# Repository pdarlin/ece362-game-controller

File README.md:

# ECE 362 Handheld Game Console

## Project Description

An RP2350-based handheld gaming console developed for Purdue University's ECE 362 Microprocessor Systems and Interfacing course.

The console features a 2.8-inch SPI TFT LCD, microSD card storage, motion controls, dual analog joysticks, a D-pad, action buttons, PWM haptic feedback, and audio output through a passive buzzer.

## Project Objectives

### 1. Game Display (SPI)
- Interface with a 2.8-inch ILI9341 TFT LCD (240 × 320).
- Display game graphics, menus, and user interfaces.
- Implement SPI communication for screen updates.

### 2. Game Storage (SPI)
- Interface with a microSD card for external storage.
- Implement file reading for game assets and data.

### 3. Motion Control (I2C)
- Interface with the MPU motion sensor using I2C.
- Read accelerometer and gyroscope data.
- Implement motion-based game controls.

### 4. Audio and Haptic Feedback (PWM)
- Generate sound effects using a passive buzzer.
- Control vibration motors using PWM.
- Implement adjustable vibration intensity for game events.

## Additional Features

- Dual analog joysticks
- D-pad and tactile action buttons
- Custom PCB designed using KiCad
- Modular firmware using the Raspberry Pi Pico SDK

## Firmware Structure

```text
firmware/
├── include/
│   ├── audio.h
│   ├── buttons.h
│   ├── display.h
│   ├── game.h
│   ├── gyro.h
│   ├── haptic.h
│   ├── joystick.h
│   └── sdcard.h
├── src/
│   ├── audio.c
│   ├── buttons.c
│   ├── display.c
│   ├── game.c
│   ├── gyro.c
│   ├── haptic.c
│   ├── joystick.c
│   ├── main.c
│   └── sdcard.c
└── platformio.ini
```

*Some firmware modules are still under development.*

## Development Tools

- **Microcontroller:** Raspberry Pi RP2350
- **Programming Language:** C
- **Framework:** Raspberry Pi Pico SDK
- **Build System:** PlatformIO
- **PCB Design:** KiCad

## Team Members

- Pierson Darling
- Tejas Menmow
- Tristan Paul
- Alex Chen

## Project Status

In development — Fall 2026.

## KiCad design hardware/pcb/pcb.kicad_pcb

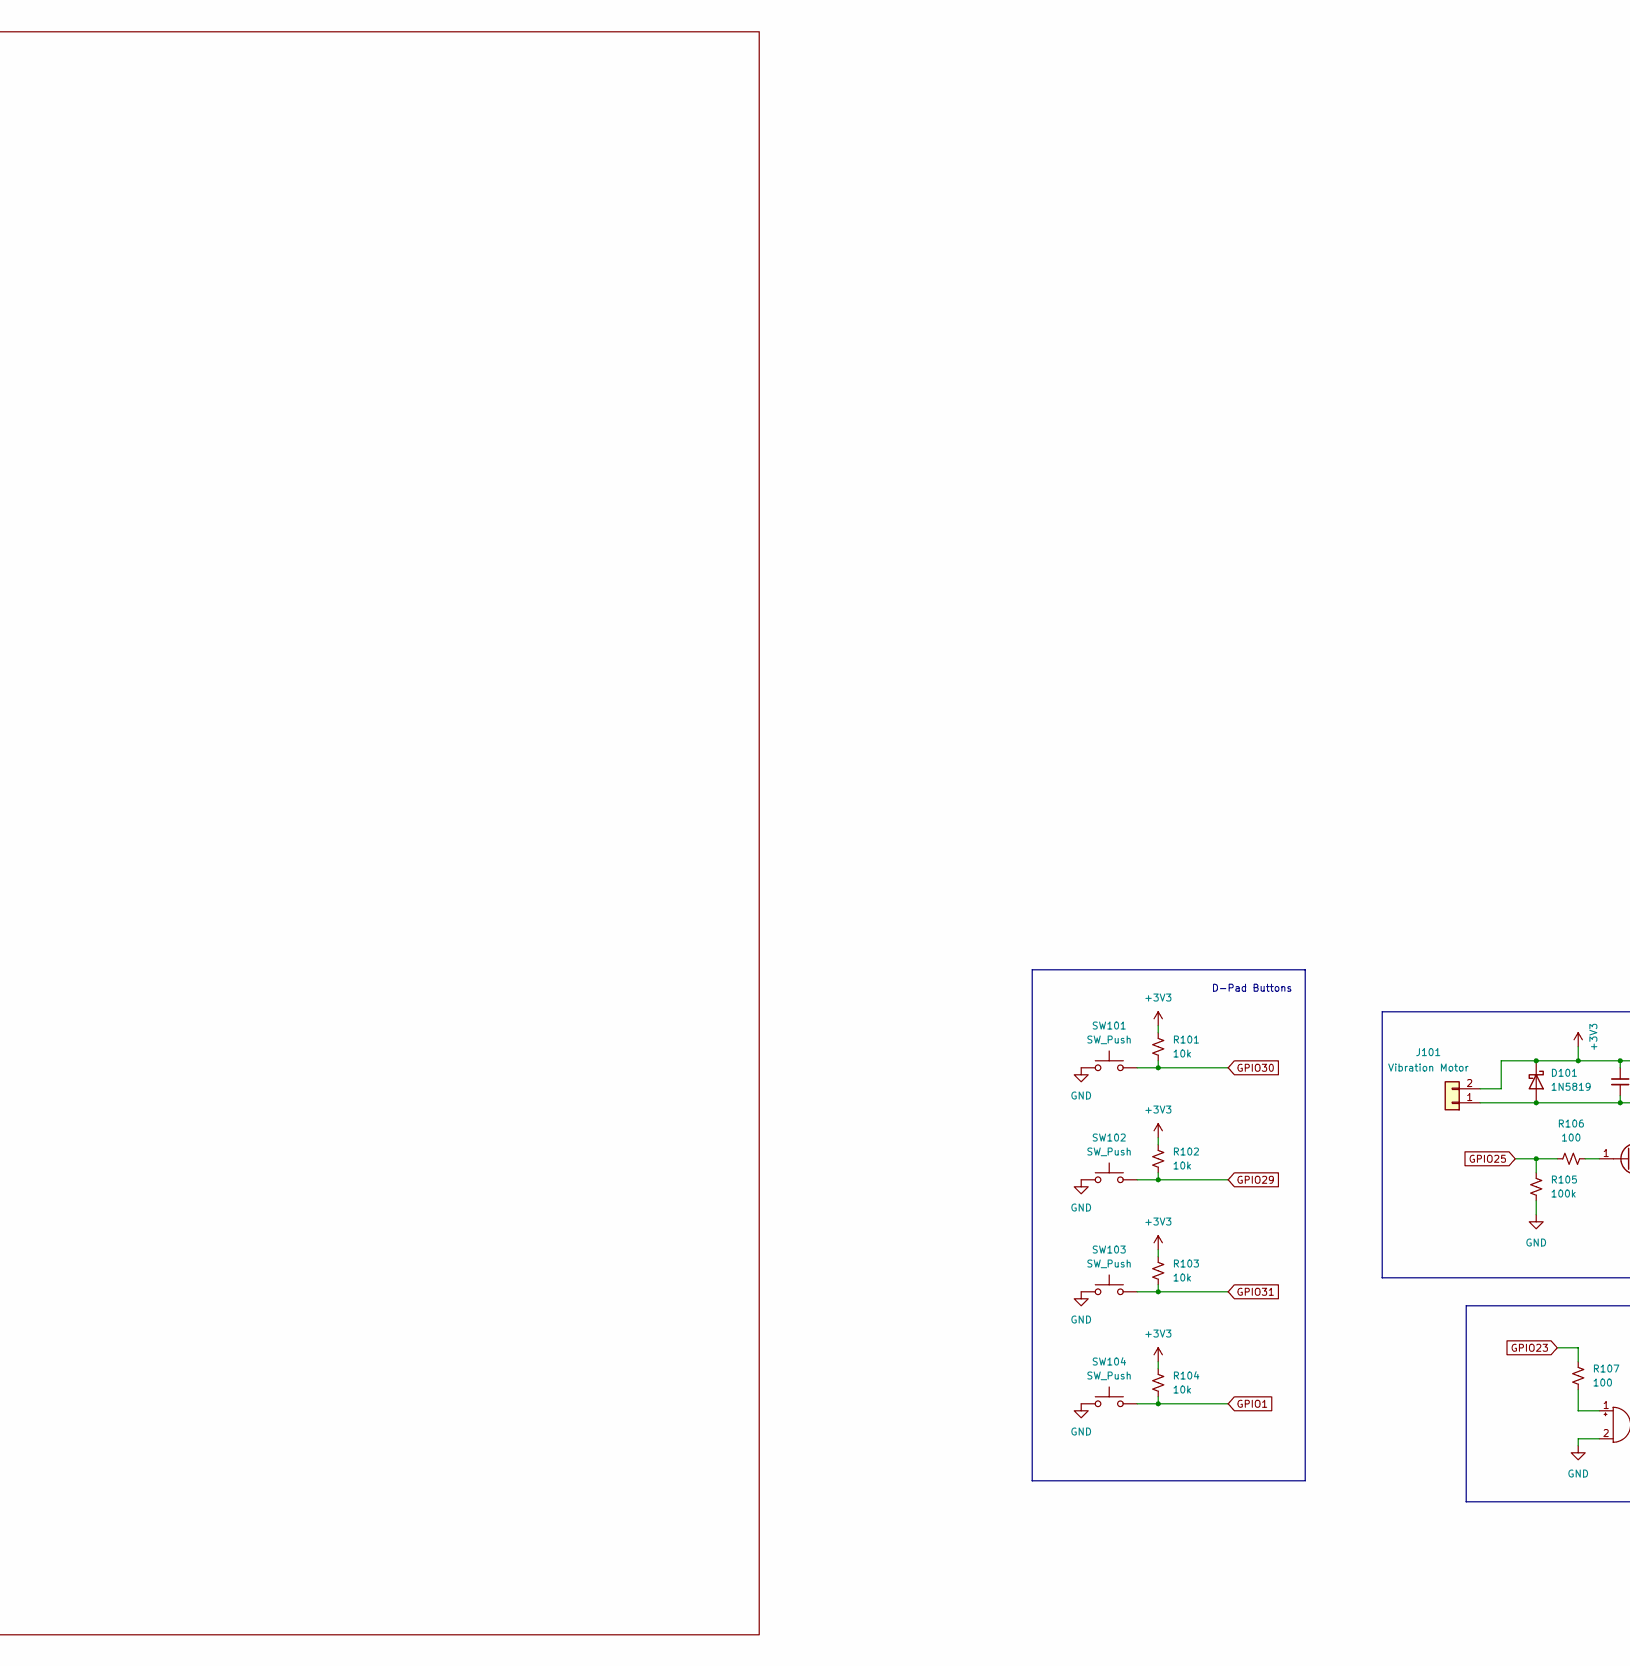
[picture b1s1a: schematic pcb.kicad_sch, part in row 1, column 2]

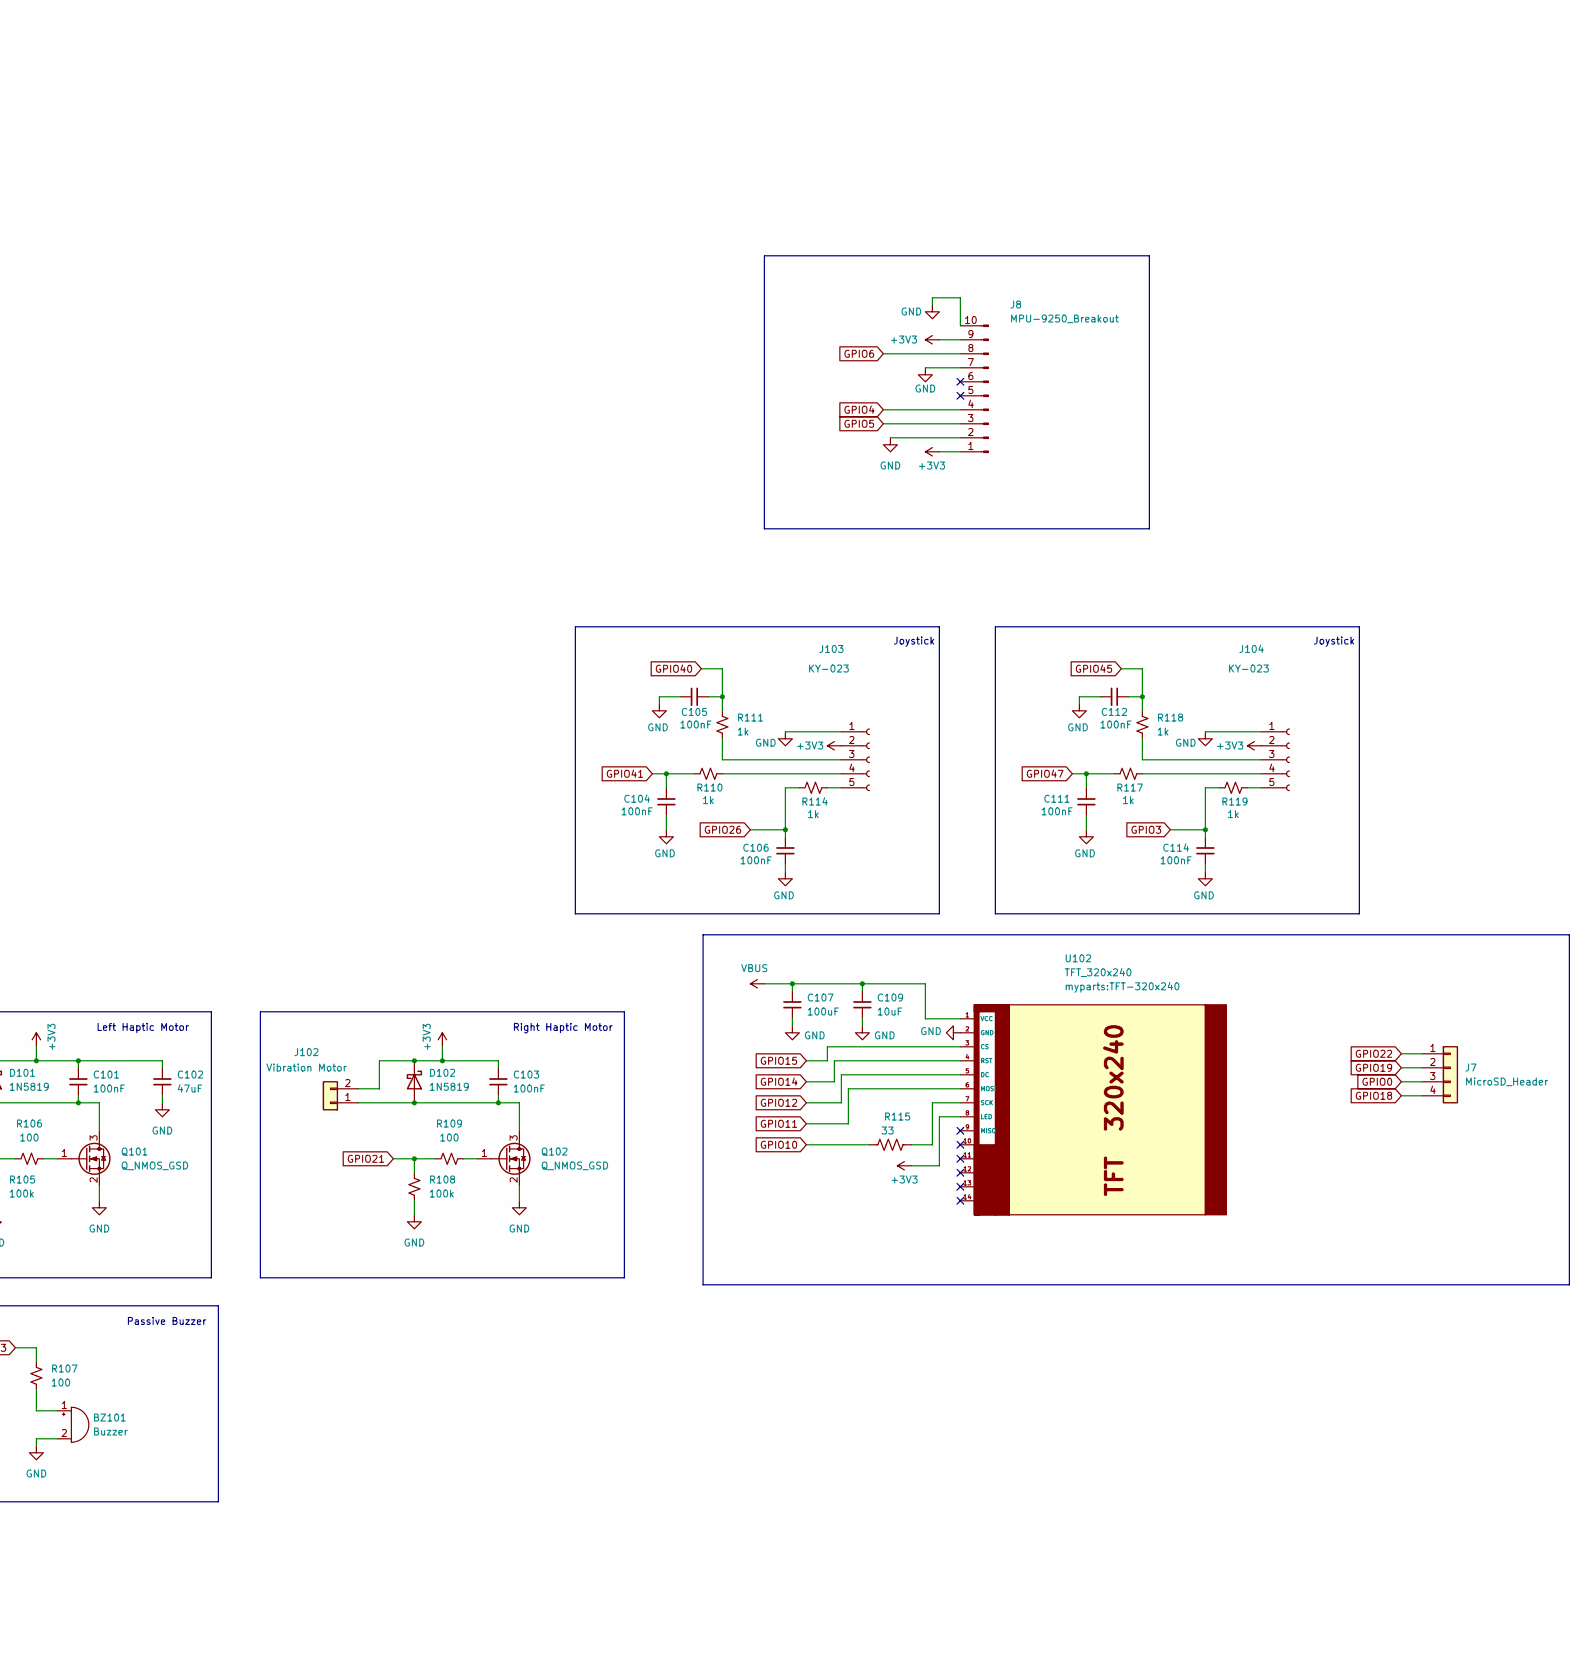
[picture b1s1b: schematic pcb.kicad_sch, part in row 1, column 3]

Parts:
BZ101: Buzzer; Buzzer_12x9.5RM7.6
C101, C103, C104, C105, C106, C111, C112, C114: 100nF; C_Disc_D5.0mm_W2.5mm_P5.00mm
C102: 47uF; CP_Radial_D6.3mm_P2.50mm
C107: 100uF; CP_Radial_D6.3mm_P2.50mm
C109: 10uF; C_Disc_D5.0mm_W2.5mm_P5.00mm
D101, D102: 1N5819; D_DO-41_SOD81_P10.16mm_Horizontal
J7: MicroSD_Header
J8: MPU-9250_Breakout
J101, J102: Vibration Motor; PinHeader_1x02_P2.54mm_Vertical
J103, J104: KY-023; PinSocket_1x05_P2.54mm_Vertical
Q101, Q102: Q_NMOS_GSD; SOT-23
R101, R102, R103, R104: 10k; R_0805_2012Metric
R105, R108: 100k; R_0805_2012Metric
R106, R107, R109: 100; R_0805_2012Metric
R110, R111, R114, R117, R118, R119: 1k; R_0805_2012Metric
R115: 33; R_0805_2012Metric
SW101, SW102, SW103, SW104: SW_Push; SW_PUSH_6mm
U102: TFT_320x240; TFT-320x240

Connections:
GND: BZ101.2 (-), C102.2, C104.1, C105.2, C106.1, C107.2, C109.2, C111.1, C112.2, C114.1, J8.2, J8.7, J8.10, J103.1, J104.1, Q101.2 (S), Q102.2 (S), R105.2, R108.2, SW101.1, SW102.1, SW103.1, SW104.1, U102.2 (GND); also elsewhere on the board
GPIO1: R104.2, SW104.2; also elsewhere on the board
GPIO3: C114.2, R119.1; also elsewhere on the board
GPIO10: R115.2; also elsewhere on the board
GPIO11: U102.6 (MOSI); also elsewhere on the board
GPIO12: U102.5 (DC); also elsewhere on the board
GPIO14: U102.4 (RST); also elsewhere on the board
GPIO15: U102.3 (CS); also elsewhere on the board
GPIO21: R108.1, R109.2; also elsewhere on the board
GPIO23: R107.2; also elsewhere on the board
GPIO25: R105.1, R106.2; also elsewhere on the board
GPIO26: C106.2, R114.1; also elsewhere on the board
GPIO29: R102.2, SW102.2; also elsewhere on the board
GPIO30: R101.2, SW101.2; also elsewhere on the board
GPIO40: C105.1, R111.2; also elsewhere on the board
GPIO41: C104.2, R110.1; also elsewhere on the board
GPIO45: C112.1, R118.2; also elsewhere on the board
GPIO47: C111.2, R117.1; also elsewhere on the board
unnamed: BZ101.1 (+), R107.1
unnamed: C101.2, D101.2 (A), J101.1, Q101.3 (D)
unnamed: C103.2, D102.2 (A), J102.1, Q102.3 (D)
unnamed: J103.3, R111.1
unnamed: J103.4, R110.2
unnamed: J103.5, R114.2
unnamed: J104.3, R118.1
unnamed: J104.4, R117.2
unnamed: J104.5, R119.2
unnamed: Q101.1 (G), R106.1
unnamed: Q102.1 (G), R109.1
unnamed: R115.1, U102.7 (SCK)

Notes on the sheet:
Joystick
Right Haptic Motor
Left Haptic Motor
D-Pad Buttons
Passive Buzzer

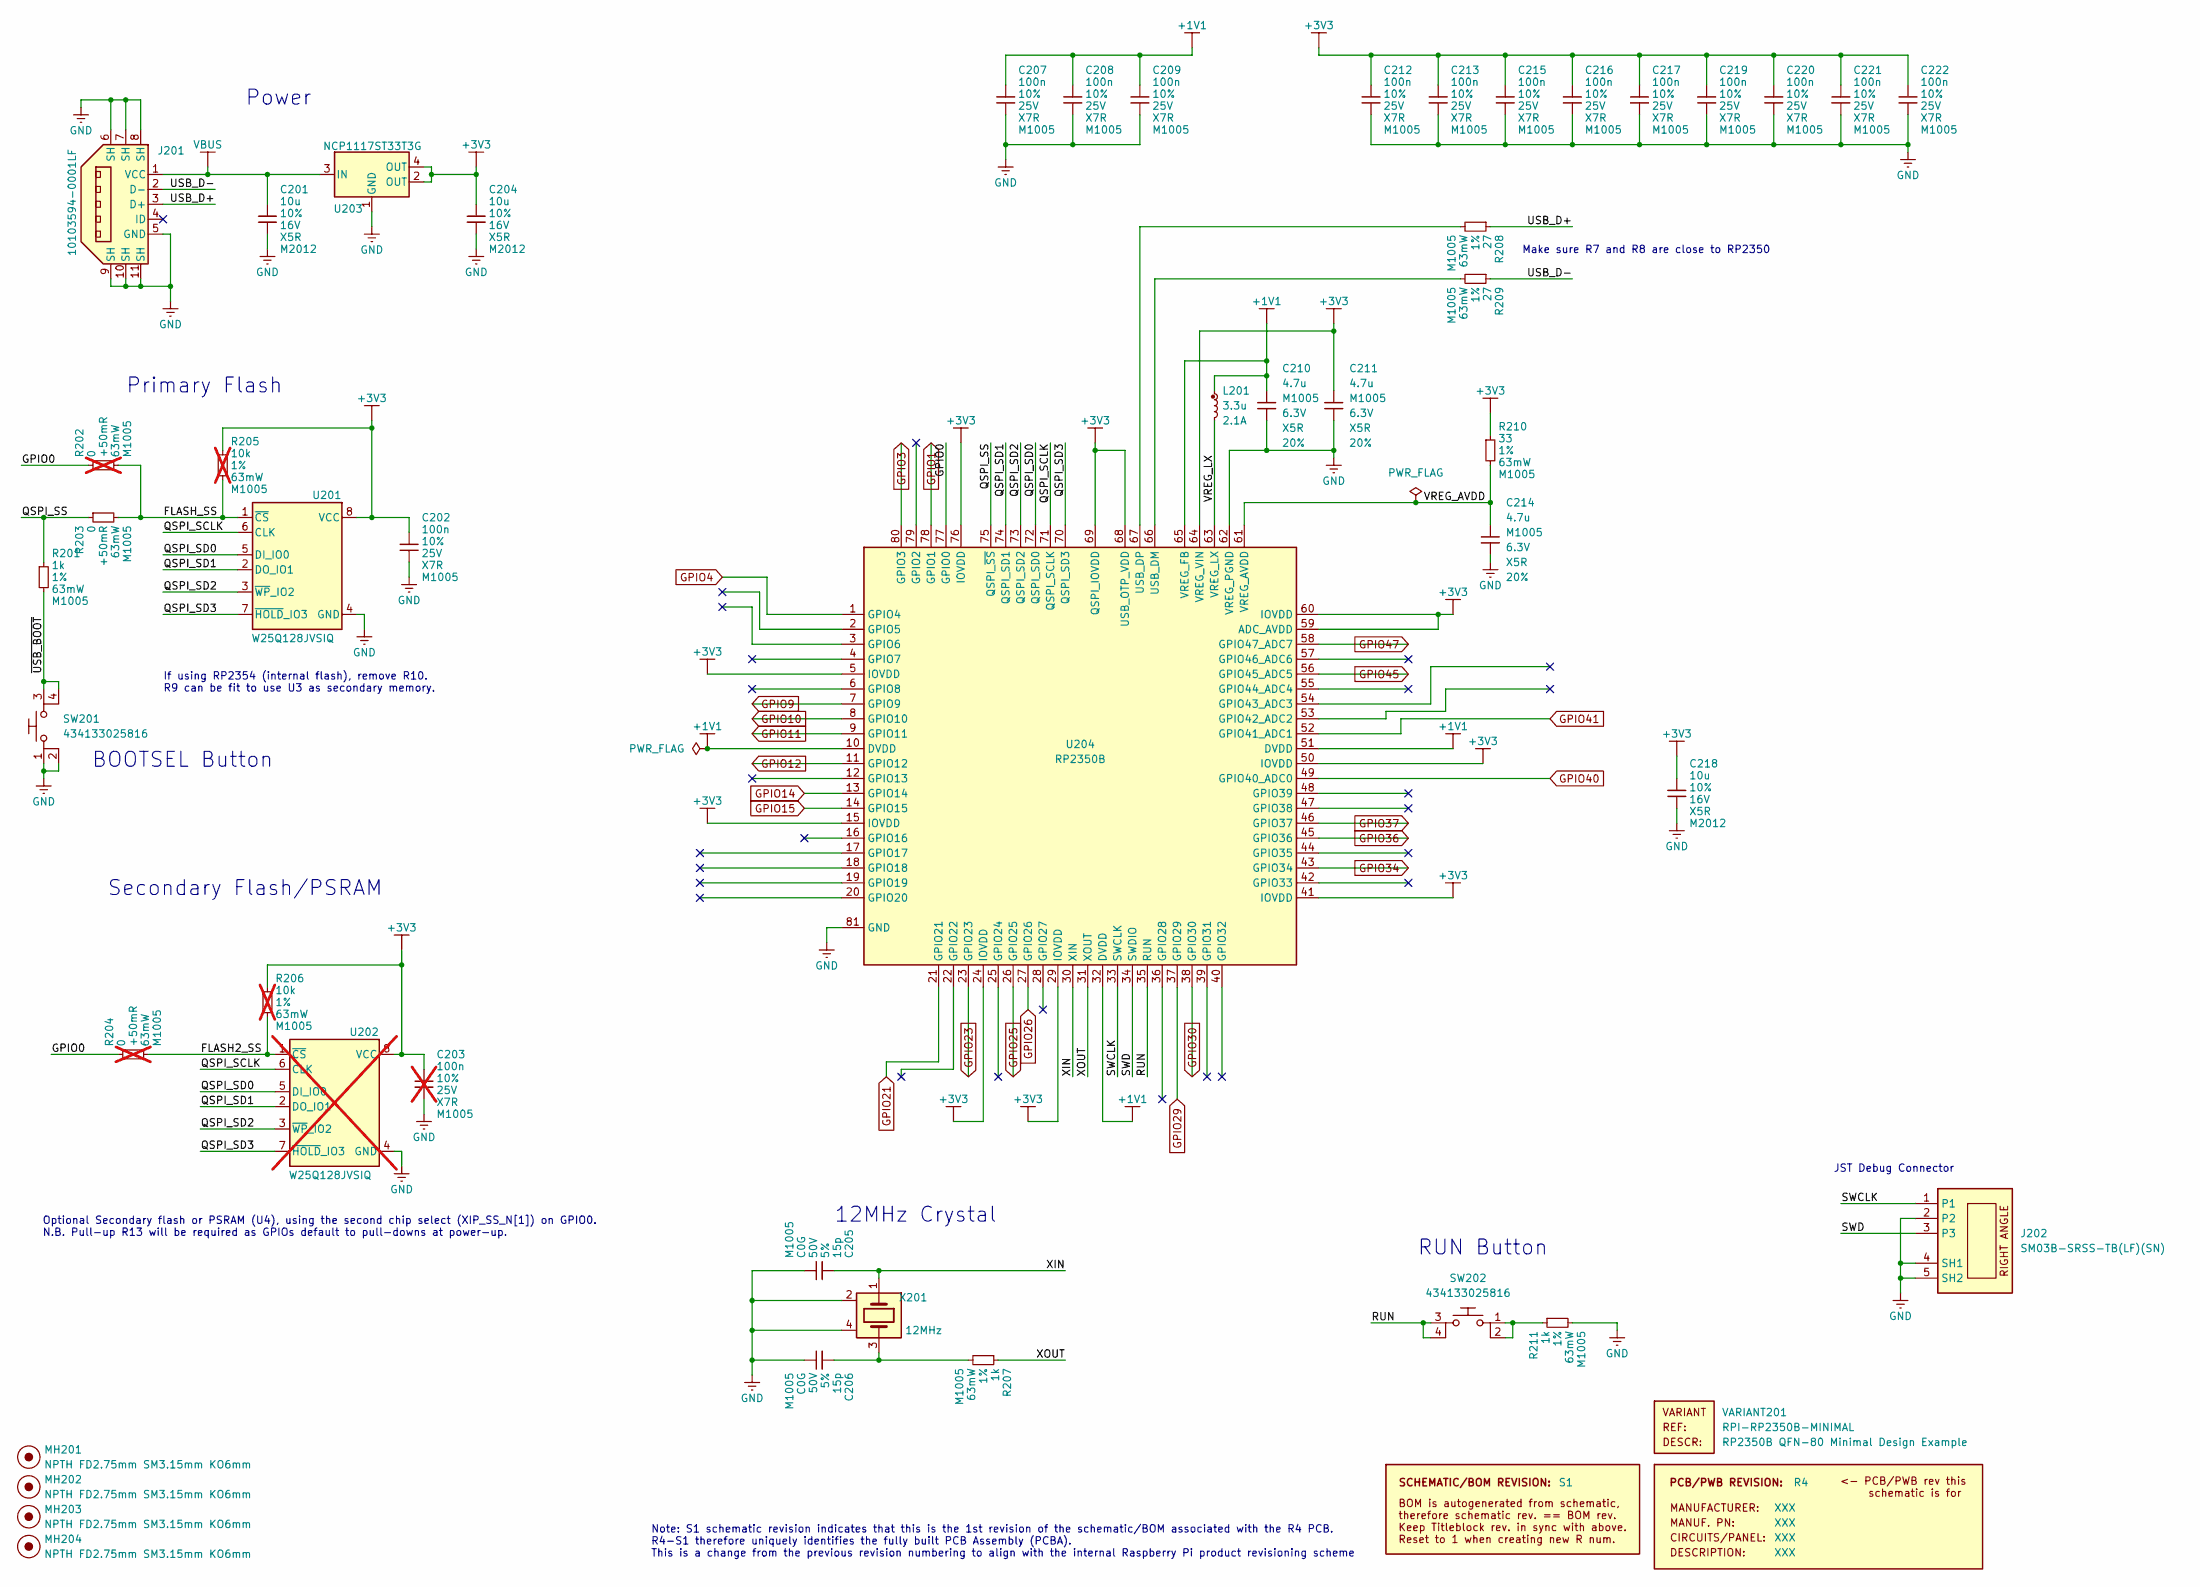
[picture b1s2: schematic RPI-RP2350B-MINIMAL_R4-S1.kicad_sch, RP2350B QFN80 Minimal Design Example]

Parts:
C201, C204, C218: 10u; generic_capc2012x125; voltage 16V; tolerance 10%; part_uid RP-01GYSK-AVBE41
C202, C207, C208, C209, C212, C213, C215, C216, C217, C219, C220, C221, C222: 100n; generic_capc1005x50; voltage 25V; tolerance 10%; part_uid RP-01BJ9Y-KRGF41
C203: 100n; generic_capc1005x50; voltage 25V; tolerance 10%; part_uid RP-01BJ9Y-KRGF41; not fitted
C205, C206: 15p; generic_capc1005x50; voltage 50V; tolerance 5%; part_uid RP-01C89W-LLY9XV
C210, C211: 4.7u; generic_capc1005x50_wide; voltage 6.3V; tolerance 20%; part_uid RP-019A1P-0C2GHY
C214: 4.7u; generic_capc1005x50; voltage 6.3V; tolerance 20%; part_uid RP-019A1P-0C2GHY
J201: 10103594-0001LF; amphenol_10103594-0001lf; part_uid RP-019A1P-1JAX7V
J202: SM03B-SRSS-TB(LF)(SN); jst_sm03b-srss-tb-lf--sn-; part_uid RP-01EKJ1-8V9SV1
L201: 3.3u; abracon_aota-b201610s3r3-101-t; tolerance 20%; part_uid RP-01GY5D-2VC7WP
MH201, MH202, MH203, MH204: NPTH FD2.75mm SM3.15mm KO6mm; none_mh_npth_fd2p75mm_sm3p15mm_ko6mm; part_uid RP-01HF5R-LCTEJS
PCB201: R4; manufacturer_pn XXX
R201, R207, R211: 1k; generic_resc1005x35; tolerance 1%; voltage 50V; part_uid RP-019A1P-4Z6ZWY
R202, R204: 0; generic_resc1005x35; tolerance +50mR; voltage 50V; part_uid RP-019A1P-4Y4V63; not fitted
R203: 0; generic_resc1005x35; tolerance +50mR; voltage 50V; part_uid RP-019A1P-4Y4V63
R205, R206: 10k; generic_resc1005x35; tolerance 1%; voltage 50V; part_uid RP-019A1P-53DHSX; not fitted
R208, R209: 27; generic_resc1005x35; tolerance 1%; voltage 50V; part_uid RP-01C89V-LTEYC4
R210: 33; generic_resc1005x35; tolerance 1%; voltage 50V; part_uid RP-019A1P-58PW9L
SBREV201: S1
SW201, SW202: 434133025816; wurthelek_434133025816; part_uid RP-01H0MT-6E9H8F
U201: W25Q128JVSIQ; generic_soic127p790x195-8; voltage 2.7-3.6V; part_uid RP-01JWD4-F1H4N9
U202: W25Q128JVSIQ; generic_soic127p790x195-8; voltage 2.7-3.6V; part_uid RP-01JWD4-F1H4N9; not fitted
U203: NCP1117ST33T3G; onsemi_ncp1117st33t3g; voltage 3.3V; part_uid RP-01JWD9-7JRX6J
U204: RP2350B; rpi_rp2350b_vias; part_uid RP-01HA9H-ABBLJN
VARIANT201: RPI-RP2350B-MINIMAL
X201: 12MHz; generic_xtalcc320x250x80-4; tolerance 30ppm; part_uid RP-01G8X7-GS352B

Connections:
+1V1: C207.1, C208.1, C209.1, C210.1, L201.1, U204.10 (DVDD), U204.32 (DVDD), U204.51 (DVDD), U204.65 (VREG_FB)
/RPCORE/FLASH2_SS: R204.2, R206.2, U202.1 (~CS)
/RPCORE/FLASH_SS: R202.2, R203.2, R205.2, U201.1 (~CS)
/RPCORE/GPIO0: R202.1, R204.1, U204.77 (GPIO0)
/RPCORE/QSPI_SCLK: U201.6 (CLK), U202.6 (CLK), U204.71 (QSPI_SCLK)
/RPCORE/QSPI_SD0: U201.5 (DI_IO0), U202.5 (DI_IO0), U204.72 (QSPI_SD0)
/RPCORE/QSPI_SD1: U201.2 (DO_IO1), U202.2 (DO_IO1), U204.74 (QSPI_SD1)
/RPCORE/QSPI_SD2: U201.3 (~WP_IO2), U202.3 (~WP_IO2), U204.73 (QSPI_SD2)
/RPCORE/QSPI_SD3: U201.7 (~HOLD_IO3), U202.7 (~HOLD_IO3), U204.70 (QSPI_SD3)
/RPCORE/QSPI_SS: R201.1, R203.1, U204.75 (QSPI_~SS)
/RPCORE/RUN: SW202.3, SW202.4, U204.35 (RUN)
/RPCORE/SWCLK: J202.1, U204.33 (SWCLK)
/RPCORE/SWD: J202.3, U204.34 (SWDIO)
/RPCORE/USB_D+: J201.3 (D+), R208.1
/RPCORE/USB_D-: J201.2 (D-), R209.1
/RPCORE/VREG_AVDD: C214.1, R210.2, U204.61 (VREG_AVDD)
/RPCORE/VREG_LX: L201.2, U204.63 (VREG_LX)
/RPCORE/XIN: C205.1, U204.30 (XIN), X201.1
/RPCORE/XOUT: R207.1, U204.31 (XOUT)
/RPCORE/~USB_BOOT: R201.2, SW201.3, SW201.4
GND: C201.2, C202.2, C203.2, C204.2, C205.2, C206.2, C207.2, C208.2, C209.2, C210.2, C211.2, C212.2, C213.2, C214.2, C215.2, C216.2, C217.2, C218.2, C219.2, C220.2, C221.2, C222.2, J201.5 (GND), J201.6 (SH), J201.7 (SH), J201.8 (SH), J201.9 (SH), J201.10 (SH), J201.11 (SH), J202.2, J202.4 (SH1), J202.5 (SH2), R211.2, SW201.1, SW201.2, U201.4 (GND), U202.4 (GND), U203.1 (GND), U204.62 (VREG_PGND), U204.81 (GND), X201.2, X201.4; also elsewhere on the board
GPIO1: U204.78 (GPIO1); also elsewhere on the board
GPIO3: U204.80 (GPIO3); also elsewhere on the board
GPIO9: U204.7 (GPIO9); also elsewhere on the board
GPIO10: U204.8 (GPIO10); also elsewhere on the board
GPIO11: U204.9 (GPIO11); also elsewhere on the board
GPIO12: U204.11 (GPIO12); also elsewhere on the board
GPIO14: U204.13 (GPIO14); also elsewhere on the board
GPIO15: U204.14 (GPIO15); also elsewhere on the board
GPIO21: U204.21 (GPIO21); also elsewhere on the board
GPIO23: U204.23 (GPIO23); also elsewhere on the board
GPIO25: U204.26 (GPIO25); also elsewhere on the board
GPIO26: U204.27 (GPIO26); also elsewhere on the board
GPIO29: U204.37 (GPIO29); also elsewhere on the board
GPIO30: U204.38 (GPIO30); also elsewhere on the board
GPIO34: U204.43 (GPIO34); also elsewhere on the board
GPIO36: U204.45 (GPIO36); also elsewhere on the board
GPIO37: U204.46 (GPIO37); also elsewhere on the board
GPIO40: U204.49 (GPIO40_ADC0); also elsewhere on the board
GPIO41: U204.52 (GPIO41_ADC1); also elsewhere on the board
GPIO45: U204.56 (GPIO45_ADC5); also elsewhere on the board
GPIO47: U204.58 (GPIO47_ADC7); also elsewhere on the board
unnamed: C206.1, R207.2, X201.3
unnamed: R211.1, SW202.1, SW202.2
unnamed: R209.2, U204.66 (USB_DM)
unnamed: R208.2, U204.67 (USB_DP)

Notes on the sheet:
Optional Secondary flash or PSRAM (U4), using the second chip select (XIP_SS_N[1]) on GPIO0. N.B. Pull-up R13 will be required as GPIOs default to pull-downs at power-up.
If using RP2354 (internal flash), remove R10. R9 can be fit to use U3 as secondary memory.
Note: S1 schematic revision indicates that this is the 1st revision of the schematic/BOM associated with the R4 PCB. R4-S1 therefore uniquely identifies the fully built PCB Assembly (PCBA). This is a change from the previous revision numbering to align with the internal Raspberry Pi product revisio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
RUN Button
Primary Flash
BOOTSEL Button
JST Debug Connector
12MHz Crystal
Make sure R7 and R8 are close to RP2350
Secondary Flash/PSRAM
Power

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
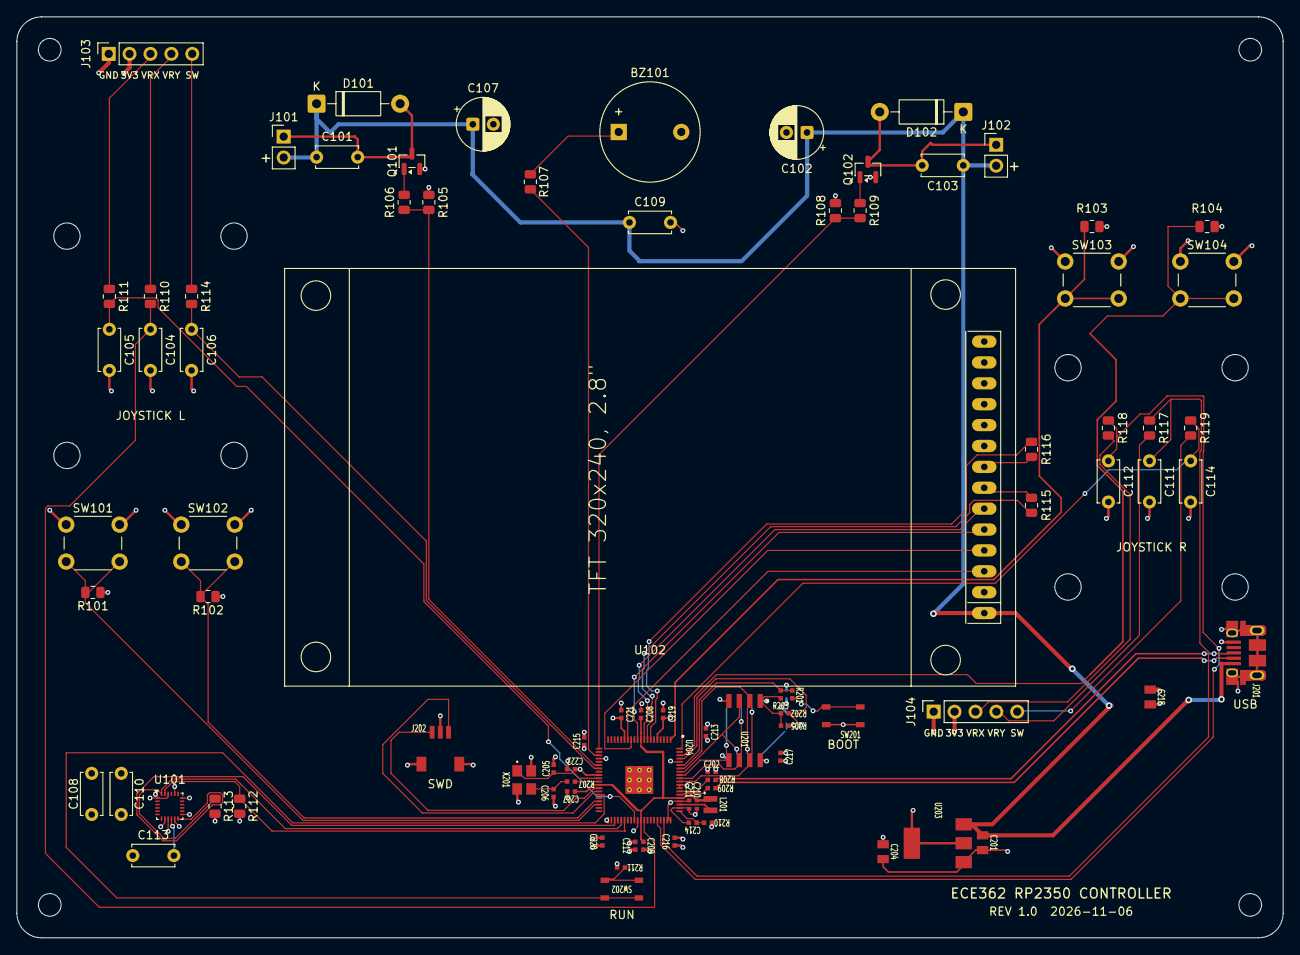
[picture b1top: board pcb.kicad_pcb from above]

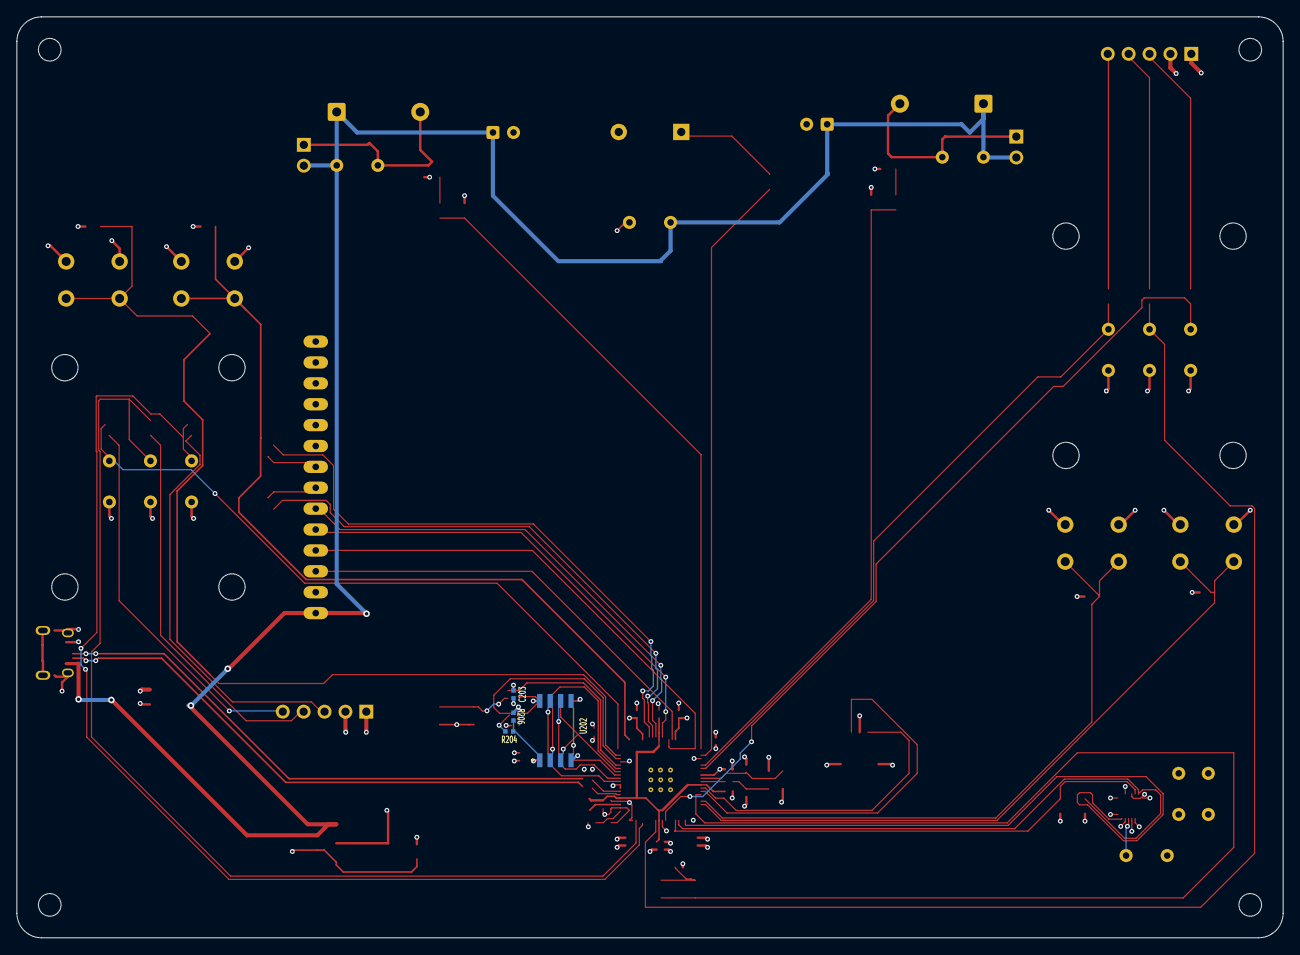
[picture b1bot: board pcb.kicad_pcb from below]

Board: 4 copper layers, 154.0 x 112.0 mm, 103 parts (4 on the bottom side), 63 nets.

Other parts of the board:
C108: 10nF; C_Disc_D5.0mm_W2.5mm_P5.00mm
C110, C113: 100nF; C_Disc_D5.0mm_W2.5mm_P5.00mm
MH1, MH2, MH3, MH4, MH5, MH6, MH7, MH8: MountingHole_3.2mm_M3
R112, R113: 4.7k; R_0805_2012Metric
R116: 1000; R_0805_2012Metric
U101: MPU-9250; InvenSense_QFN-24_3x3mm_P0.4mm

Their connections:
GND: C108.2, C110.2, C113.1, U101.9 (AD0/MISO), U101.11 (FSYNC), U101.18 (GND), U101.20 (RESV_GND); also elsewhere on the board
GPIO9: R116.2; also elsewhere on the board
GPIO34: U101.12 (INT); also elsewhere on the board
GPIO36: R113.1, U101.24 (SDA/MOSI); also elsewhere on the board
GPIO37: R112.1, U101.23 (SCL/SCLK); also elsewhere on the board
unnamed: C113.2, U101.10 (REGOUT)
